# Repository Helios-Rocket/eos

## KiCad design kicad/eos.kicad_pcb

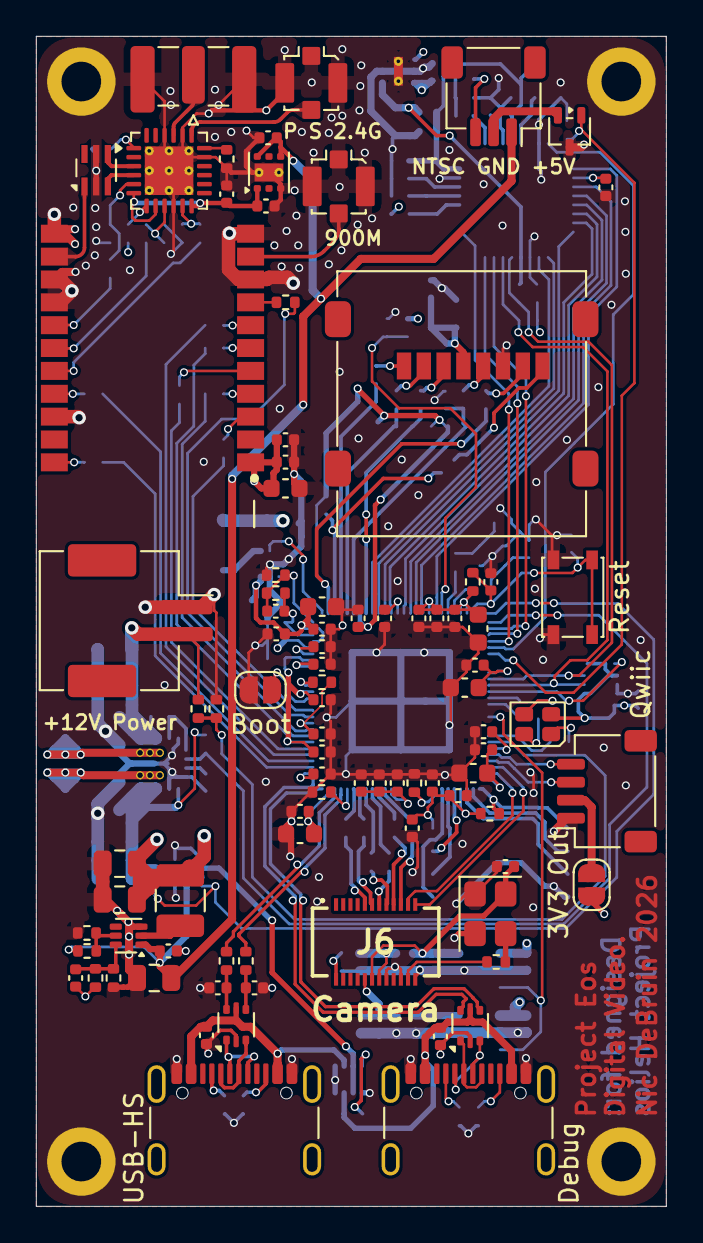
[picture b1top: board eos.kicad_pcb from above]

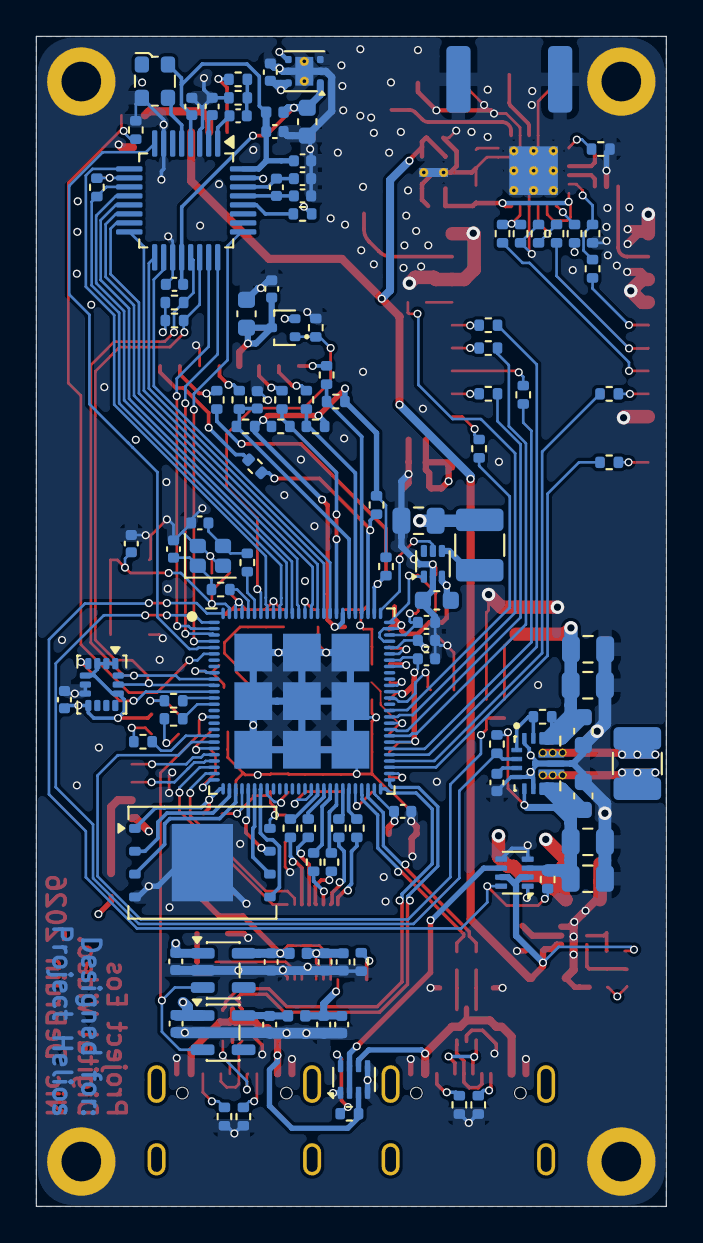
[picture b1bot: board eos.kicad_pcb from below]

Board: 4 copper layers, 35.0 x 65.0 mm, 206 parts (113 on the bottom side), 161 nets.

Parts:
C1, C9, C36, C37, C38, C39, C40, C44, C55, C57, C64, C65, C66, C69, C70, C72, C73, C75, C78, C80, C81, C82: 1u; C_0402_1005Metric
C2, C5, C22, C23, C32, C42, C47, C79, C85: 10u; C_0603_1608Metric
C3, C4: 10u; C_0805_2012Metric
C6, C7, C14, C15, C16, C20: 22u; C_0805_2012Metric
C8, C12, C17, C21, C24, C25, C26, C27, C28, C33, C34, C35, C41, C43, C45, C46, C48, C49, C51, C54, C56, C59, C60, C61, C62, C63, C67, C68, C71, C74, C76, C84, C86: 0.1u; C_0402_1005Metric
C10, C11, C31: TBD; C_0402_1005Metric
C13: 10p; C_0402_1005Metric
C18: 22p; C_0402_1005Metric
C19, C52: 4.7u; C_0603_1608Metric
C29, C30: 16p; C_0402_1005Metric
C50, C53, C58, C77, C83: 10n; C_0402_1005Metric
D1: LED_RGBA; LED_Cree-PLCC4_2x2mm_CW
FB1, FB2, FB3: BLM15BB470SN1D; L_0402_1005Metric
H1, H2, H3, H4: MountingHole_Pad; MountingHole_2.2mm_M2_DIN965_Pad
J1: Debug; USB_C_Receptacle_GCT_USB4105-xx-A_16P_TopMnt_Horizontal
J2: USB-HS; USB_C_Receptacle_GCT_USB4105-xx-A_16P_TopMnt_Horizontal
J3: Power In; JST_ZE_SM02B-ZESS-TB_1x02-1MP_P1.50mm_Horizontal
J4: Qwiic; JST_SH_SM04B-SRSS-TB_1x04-1MP_P1.00mm_Horizontal
J5: Micro_SD_Card; microSD_HC_Molex_47219-2001
J6: Camera; DF30FC24DS04V81
J8: Split 4; JST_SH_SM03B-SRSS-TB_1x03-1MP_P1.00mm_Horizontal
J9: 2.4G Backup; U.FL_Molex_MCRF_73412-0110_Vertical
J10: 2.4G; SMA_Samtec_SMA-J-P-H-ST-EM1_EdgeMount
J11: 915M; U.FL_Molex_MCRF_73412-0110_Vertical
JP1: 3V3 Out; SolderJumper-2_P1.3mm_Open_RoundedPad1.0x1.5mm
JP2: Boot; SolderJumper-2_P1.3mm_Open_RoundedPad1.0x1.5mm
L1: 1.5u; L_1210_3225Metric
L2: 3.3u; L_1210_3225Metric
L3: 2.2u; L_1210_3225Metric
Q1: PMOS; SOT-416
Q2: NMOS; SOT-323_SC-70
R1, R4, R10, R11: 5.1k; R_0402_1005Metric
R2, R8, R9, R17, R22, R37, R38, R39, R51, R54, R56, R60, R70, R71, R72, R73: 10k; R_0402_1005Metric
R3, R19: 100k; R_0402_1005Metric
R5, R6, R7: 330R; R_0402_1005Metric
R12, R13: 22R; R_0402_1005Metric
R14: 76.8k; R_0402_1005Metric
R15: 45.3k; R_0402_1005Metric
R16: 30k; R_0402_1005Metric
R18: 340k; R_0402_1005Metric
R20, R21: 499k; R_0402_1005Metric
R23, R24, R25, R26, R27, R28: 51k; R_0402_1005Metric
R29, R30, R31, R32, R33, R34, R35, R36, R40, R41, R42, R43, R44, R45, R55: 0R; R_0402_1005Metric
R46, R47: 4.02k; R_0402_1005Metric
R48, R49: 37R4; R_0402_1005Metric
R50: 1k; R_0402_1005Metric
R52, R53: 2.2k; R_0402_1005Metric
R57, R58, R59, R61, R63, R64, R65, R66, R67, R68, R69: 470R; R_0402_1005Metric
R74: 50R0; R_0402_1005Metric
SW1: Reset; SW_SPST_PTS810
U1: TPS63071; VREG_TPS630701RNMR
U2, U5: USBLC6-2P6; SOT-666
U3, U4: LM66200; SOT-583-8
U6: TPS56425x; SOT-563
U7: LSM6DSV32X; LGA-14_3x2.5mm_P0.5mm_LayoutBorder3x4y
U8: TLV62569DRL; SOT-563
U9: GD25Q256EY; WSON-8-1EP_8x6mm_P1.27mm_EP3.4x4.3mm
U10: ESP32-P4
U11: TVP5150AM1; TQFP-32_5x5mm_P0.5mm
U12: TLV73328PDBV; SOT-23-5
U13: TLV73315PDBV; SOT-23-5
U14: TPS7A26; WSON-6-1EP_2x2mm_P0.65mm_EP1x1.6mm_ThermalVias
U15: TLV75740PDRV; WSON-6-1EP_2x2mm_P0.65mm_EP1x1.6mm_ThermalVias
U16: 2450BL15B050; Balun_Johanson_5400BL15B050E
U17: SE2436L; QFN-24-1EP_4x4mm_P0.5mm_EP2.7x2.7mm_ThermalVias
U18: WIO-LR2021; Wio-LR2021_V1
Y1: 40MHz; Crystal_SMD_2016-4Pin_2.0x1.6mm
Y2: 14.31818MHz; Oscillator_SMD_ECS_2520MV-xxx-xx-4Pin_2.5x2.0mm
Y3: ECS-TXO-32CSMV; Crystal_SMD_3225-4Pin_3.2x2.5mm

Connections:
5V_PG: R3.2, U1.2 (PG), U10.1 (GPIO1)
+1V5: C75.1, C76.1, FB2.2, J6.20
+1V8: C63.1, C79.1, FB3.1, U11.20 (DVDD), U14.1 (OUT)
+2V8: C70.1, C77.1, FB1.1, J6.19, U12.5 (OUT), Y3.4 (VDD)
+3.3V: C13.1, C15.1, C16.1, C17.1, C19.1, C23.1, C24.1, C25.1, C26.1, C32.1, C33.1, C35.1, C42.1, C43.1, C46.1, C49.1, C52.1, C53.1, C54.1, C62.1, C69.1, C73.1, C78.1, C83.1, C84.1, C85.1, D1.4 (A), JP1.2 (B), L2.2, Q1.2 (S), R15.1, R37.1, R39.2, R51.1, R52.1, R53.1, R54.1, R60.1, U7.1 (SDO/SA0), U7.2 (SDX), U7.3 (SCX), U7.5 (VDDIO), U7.8 (VDD), U7.12 (CS), U8.3 (VIN), U10.9 (VDD_LP), U10.21 (VDD_IO_0), U10.51 (VDD_USBPHY), U10.62 (VDD_IO_4), U10.75 (VDD_LDO), U10.77 (VDD_DCDCC), U10.96 (VDD_IO_6), U10.101 (VDD_ANA), U10.102 (VDD_BAT), U11.10 (IO_DVDD), U12.1 (IN), U13.1 (IN), U14.4 (EN), U14.6 (IN), U18.1 (VCC)
+4V: C82.1, C86.1, U15.1 (OUT), U17.6 (VCC), U17.8 (VCC), U17.12 (VCC)
+5V: C12.1, C14.1, C81.1, J8.1, R14.1, U3.2 (VOUT), U3.7 (VOUT), U6.1 (VIN), U15.4 (EN), U15.6 (IN)
+5VP: C2.1, C6.1, C7.1, R3.1, R8.1, U1.5 (FB), U1.7 (VOUT), U3.3 (VIN1)
+BATT: C3.1, C4.1, C5.1, J3.2, R2.1, R18.1, U1.12 (VIN)
/cameras/+2V8F: C71.1, C72.1, FB1.2, J6.18
/cameras/MCLK: J6.14, R55.2
/cameras/NTSC_IN: J8.3, R48.1
/mcu/BOOT_MODE: JP2.2 (B), U10.66 (GPIO35)
/mcu/CLK+: R42.1, U10.44 (CSI_CLKP)
/mcu/CLK-: R43.1, U10.45 (CSI_CLKN)
/mcu/D0+: R41.1, U10.43 (CSI_DATAP0)
/mcu/D0-: R40.1, U10.42 (CSI_DATAN0)
/mcu/D1+: R45.1, U10.47 (CSI_DATAP1)
/mcu/D1-: R44.1, U10.46 (CSI_DATAN1)
/mcu/EN_DCDC: U8.5 (EN), U10.79 (EN_DCDC)
/mcu/FB_DCDC: C18.2, R20.2, R21.1, U8.1 (FB), U10.78 (FB_DCDC)
/mcu/FLASH_CLK: U9.6 (SCLK), U10.32 (FLASH_CK)
/mcu/FLASH_DI: U9.5 (SI/IO0), U10.33 (FLASH_D)
/mcu/FLASH_DO: U9.2 (SO/IO1), U10.28 (FLASH_Q)
/mcu/FLASH_HOLD: U9.7 (~HOLD/~RESET/IO3), U10.31 (FLASH_HOLD)
/mcu/FLASH_~CS: R38.2, U9.1 (~CS), U10.27 (FLASH_CS)
/mcu/FLASH_~WP: U9.3 (~WP/IO2), U10.29 (FLASH_WP)
/mcu/SD_CLK: C31.1, R26.2, R32.2, U10.84 (GPIO43)
/mcu/SD_CMD: R25.2, R31.2, U10.86 (GPIO44)
/mcu/SD_D0: R27.2, R34.2, U10.80 (GPIO39)
/mcu/SD_D1: R28.2, R36.2, U10.81 (GPIO40)
/mcu/SD_D2: R23.2, R29.2, U10.82 (GPIO41)
/mcu/SD_D3: R24.2, R30.2, U10.83 (GPIO42)
/mcu/SD_RST: Q1.1 (G), R22.1, U10.98 (ADC2_CHANNEL5)
/mcu/~ESP_EN: C40.1, C50.1, R37.2, SW1.2, U10.103 (CHIP_PU)
/radio/2.4G_Backup: J9.1 (In), U17.19 (ANT2)
/radio/2.4G_Main: J10.1 (In), U17.21 (ANT1)
/radio/LNA_EN: R63.2, R73.1, U17.11 (CPS)
/radio/RF+: U16.4, U17.3 (TRP)
/radio/RF-: U16.3, U17.4 (TRN)
/radio/RX_EN: R59.2, R71.1, U17.5 (CRX)
/radio/TX_EN: R61.2, R72.1, U17.9 (CTX)
BATT_ADC: R18.2, R19.1, U10.20 (ADC1_CHANNEL3)
CSI_CLK+: J6.7, R42.2
CSI_CLK-: J6.8, R43.2
CSI_D0+: J6.9, R41.2
CSI_D0-: J6.10, R40.2
CSI_D1+: J6.5, R45.2
CSI_D1-: J6.6, R44.2
EXT_SCL: J4.4, U10.22 (GPIO20/ADC1_CHANNEL4)
EXT_SDA: J4.3, U10.23 (GPIO21/ADC1_CHANNEL5)
FID: U10.2 (GPIO2), U11.23 (FID)
GND: C1.2, C2.2, C3.2, C4.2, C5.2, C6.2, C7.2, C8.2, C9.2, C10.1, C11.2, C12.2, C14.2, C15.2, C16.2, C17.2, C19.2, C20.2, C21.2, C22.2, C23.2, C24.2, C25.2, C26.2, C27.2, C28.2, C29.1, C30.1, C31.2, C32.2, C33.2, C34.2, C35.2, C36.2, C37.2, C38.2, C39.2, C40.2, C41.2, C42.2, C43.2, C44.2, C45.2, C46.2, C47.2, C48.2, C49.2, C50.2, C51.2, C52.2, C53.2, C54.2, C55.2, C56.2, C57.2, C58.2, C59.2, C60.2, C61.2, C62.2, C63.2, C65.2, C66.2, C68.2, C69.2, C70.2, C71.2, C72.2, C73.2, C74.2, C75.2, C76.2, C77.2, C78.2, C79.2, C80.2, C81.2, C82.2, C83.2, C84.2, C85.2, C86.2, H1.1 (1_1), H2.1 (1_1), H3.1 (1_1), H4.1 (1_1), J1.A1 (GND), J1.A12 (GND), J1.B1 (GND), J1.B12 (GND), J2.A1 (GND), J2.A12 (GND), J2.B1 (GND), J2.B12 (GND), J3.1, J4.1, J5.6 (VSS), J6.13, J6.15, J6.17, J9.2 (Ext), J10.2 (Ext), J11.2 (Ext), JP2.1 (A), Q2.3 (S), R1.2, R4.2, R10.2, R11.2, R16.2, R17.2, R19.2, R21.2, R22.2, R46.2, R47.2, R49.1, R50.1, R56.2, R70.2, R71.2, R72.2, R73.2, R74.2, SW1.1, U1.4 (GND), U1.6 (FB2), U1.10 (GND), U1.15 (VSEL), U2.2 (GND), U3.1 (GND), U3.4 (~ON), U3.5 (GND), U4.1 (GND), U4.4 (~ON), U4.5 (GND), U5.2 (GND), U6.3 (GND), U7.6 (GND), U7.7 (GND), U8.2 (GND), U9.4 (VSS), U9.9 (PAD), U10.105 (GND), U11.3 (PLL_AGND), U11.7 (AGND), U11.19 (DGND), U11.31 (CH_AGND), U12.2 (GND), U13.2 (GND), U14.2 (GND), U14.3 (PG), U14.5 (GND), U14.7 (GND), U15.3 (GND), U15.7 (GND), U16.2 (GND), U16.5 (GND), U17.10 (GND), U17.17 (GND), U17.20 (GND), U17.22 (GND), U17.25 (GND), U18.9 (GND), U18.11 (GND), U18.12 (GND), U18.14 (GND), U18.15 (GND), U18.20 (GND), Y1.2 (G), Y1.4 (G), Y2.2 (GND), Y3.1 (GND), Y3.2 (GND)
HSYNC: U10.4 (GPIO4), U11.25 (HSYNC)
IMU_INT1: U7.4 (INT1), U10.12 (GPIO11)
IO0_PowerEN: U10.16 (GPIO15), U12.3 (EN), U13.3 (EN)
LED_BLUE: R7.2, U10.13 (GPIO12)
LED_GREEN: R6.2, U10.14 (GPIO13)
LED_RED: R5.2, U10.19 (GPIO18/ADC1_CHANNEL2)
LR_BUSY: R57.2, U10.63 (GPIO32)
LR_IRQ1: R67.2, U10.55 (GPIO26/USB1P1_N1)
LR_IRQ2: R65.2, U10.56 (GPIO27/USB1P1_P1)
LR_MISO: R64.1, U10.61 (GPIO31)
LR_MOSI: R66.1, U10.58 (GPIO29)
LR_SCK: R68.1, U10.60 (GPIO30)
LR_~CS: R69.1, U10.57 (GPIO28)
LR_~RESET: R58.2, U10.64 (GPIO33)
MIPI_I2C_SCL: J6.11, U10.25 (GPIO23/ADC1_CHANNEL7)
MIPI_I2C_SDA: J6.12, U10.24 (GPIO22/ADC1_CHANNEL6)
unnamed: C10.2, R12.1, U5.6 (I/O1)
unnamed: C11.1, R13.1, U5.4 (I/O2)
unnamed: C29.2, R33.1, Y1.3
unnamed: C30.2, R35.1, Y1.1
unnamed: C67.1, R48.2, R49.2
unnamed: D1.3 (BK), R7.1
unnamed: D1.2 (GK), R6.1
unnamed: D1.1 (RK), R5.1
unnamed: J1.A5 (CC1), R1.1
unnamed: J1.B5 (CC2), R4.1
unnamed: J1.A6 (D+), J1.B6 (D+), U2.1 (I/O1)
unnamed: J1.A7 (D-), J1.B7 (D-), U2.3 (I/O2)
unnamed: J2.A5 (CC1), R10.1
unnamed: J2.B5 (CC2), R11.1
unnamed: J2.A6 (D+), J2.B6 (D+), U5.1 (I/O1)
unnamed: J2.A7 (D-), J2.B7 (D-), U5.3 (I/O2)
unnamed: J4.2, JP1.1 (A)
unnamed: J5.5 (CLK), R32.1
unnamed: J5.3 (CMD), R31.1
unnamed: J5.7 (DAT0), R34.1
unnamed: J5.8 (DAT1), R36.1
unnamed: J5.1 (DAT2), R29.1
unnamed: J5.2 (DAT3/CD), R30.1
unnamed: C21.1, C22.1, J5.4 (VDD), Q1.3 (D)
unnamed: J6.24, R50.2
unnamed: J8.2, Q2.2 (D)
unnamed: J11.1 (In), U18.10 (Sub-G_RF)
unnamed: R2.2, U1.1 (PS/SYNC), U1.14 (EN)
unnamed: L1.1, U1.11 (L1)
unnamed: L1.2, U1.9 (L2)
unnamed: C8.1, U1.3 (VAUX)
unnamed: R9.2, U4.8 (ST)
unnamed: R14.2, R16.1, U6.5 (EN)
unnamed: C13.2, R15.2, R17.1, U6.6 (FB)
unnamed: L2.1, U6.2 (SW)
unnamed: L3.1, U8.4 (SW)
unnamed: R47.1, U10.48 (CSI_REXT)
unnamed: R46.1, U10.34 (DSI_REXT)
unnamed: R39.1, U10.68 (GPIO36)
unnamed: R33.2, U10.99 (XTAL_N)
unnamed: R35.2, U10.100 (XTAL_P)
unnamed: C67.2, U11.1 (AIP1A)
unnamed: C68.1, U11.2 (AIP1B)
unnamed: C64.2, C66.1, U11.30 (REFM)
unnamed: C64.1, C65.1, U11.29 (REFP)
unnamed: U11.5 (OSC), Y2.3 (OUT)
unnamed: R54.2, U11.28 (~PDN)
unnamed: C74.1, FB2.1, U13.5 (OUT)
unnamed: R70.1, U17.1 (ANT_SEL)
unnamed: R74.1, U17.18 (AUX)
unnamed: R60.2, U17.7 (CSD)
unnamed: U16.1, U18.13 (2.4G_RF)
unnamed: R57.1, U18.8 (BUSY)
unnamed: R67.1, U18.22 (DIO7)
unnamed: R65.1, U18.19 (DIO8)
unnamed: R63.1, U18.18 (DIO9)
unnamed: R61.1, U18.17 (DIO10)
unnamed: R59.1, U18.16 (DIO11)
unnamed: R64.2, U18.4 (MISO)
unnamed: R66.2, U18.5 (MOSI)
unnamed: R68.2, U18.6 (SCK)
unnamed: R69.2, U18.7 (~CS)
unnamed: R58.1, U18.3 (~RESET)
unnamed: R55.1, Y3.3 (OUT)
ONBOARD_SCL: R53.2, U7.13 (SCL), U10.11 (GPIO10), U11.22 (SCL)
ONBOARD_SDA: R52.2, U7.14 (SDA), U10.10 (GPIO9), U11.21 (SDA)
ON_BATT: R8.2, U3.8 (ST), U10.104 (GPIO0)
SCLK: U10.97 (GPIO53/ADC2_CHANNEL4), U11.9 (SCLK)
SPLIT4_EN: Q2.1 (G), R56.1, U10.6 (GPIO6)
USB_DEBUG+: U2.6 (I/O1), U10.53 (USB1P1_P0)
USB_DEBUG-: U2.4 (I/O2), U10.52 (USB1P1_N0)
USB_HS+: R12.2, U10.50 (USB-DP)
USB_HS-: R13.2, U10.49 (USB-DM)
VDD: C18.1, C20.1, C27.1, C34.1, C47.1, C48.1, C51.1, L3.2, R20.1, U10.26 (VDD_HP_0), U10.54 (VDD_HP_1), U10.76 (VDD_HP_2), U10.91 (VDD_HP_3)
VDDA: C60.1, C61.1, C80.1, FB3.2, U11.4 (PLL_AVDD), U11.32 (CH_AVDD), Y2.4 (VDD)
VFLASH: C39.1, C41.1, C55.1, C56.1, R38.1, U9.8 (VCC), U10.30 (VDD_FLASH_IO), U10.71 (VDDO_FLASH)
VMIPI: C37.1, C57.1, C58.1, C59.1, U10.41 (VDD_MIPI_DPHY), U10.73 (VDDO_3)
VPSRAM: C38.1, C44.1, C45.1, U10.59 (VDD_PSRAM_0), U10.67 (VDD_PSRAM_1), U10.72 (VDDO_PSRAM)
VSYNC: U10.3 (GPIO3), U11.24 (VSYNC)
VUSB: U3.6 (VIN2), U4.2 (VOUT), U4.7 (VOUT)
VUSB1: C1.1, J1.A4 (VBUS), J1.A9 (VBUS), J1.B4 (VBUS), J1.B9 (VBUS), R9.1, U2.5 (VBUS), U4.3 (VIN1)
VUSB2: C9.1, J2.A4 (VBUS), J2.A9 (VBUS), J2.B4 (VBUS), J2.B9 (VBUS), U4.6 (VIN2), U5.5 (VBUS)
V_SD: C28.1, C36.1, R23.1, R24.1, R25.1, R26.1, R27.1, R28.1, U10.74 (VDDO_4), U10.85 (VDD_IO_5)
Y0: U10.87 (GPIO45), U11.18 (YOUT0)
Y1: U10.88 (GPIO46), U11.17 (YOUT1)
Y2: U10.89 (GPIO47), U11.16 (YOUT2)
Y3: U10.90 (GPIO48), U11.15 (YOUT3)
Y4: U10.92 (GPIO49/ADC2_CHANNEL0), U11.14 (YOUT4)
Y5: U10.93 (GPIO50/ADC2_CHANNEL1), U11.13 (YOUT5)
Y6: U10.94 (GPIO51/ADC2_CHANNEL2), U11.12 (YOUT6)
Y7: R51.2, U10.95 (GPIO52/ADC2_CHANNEL3), U11.11 (YOUT7/I2CSEL)
~TVP_RESET: U10.5 (GPIO5), U11.8 (~RESETB)
